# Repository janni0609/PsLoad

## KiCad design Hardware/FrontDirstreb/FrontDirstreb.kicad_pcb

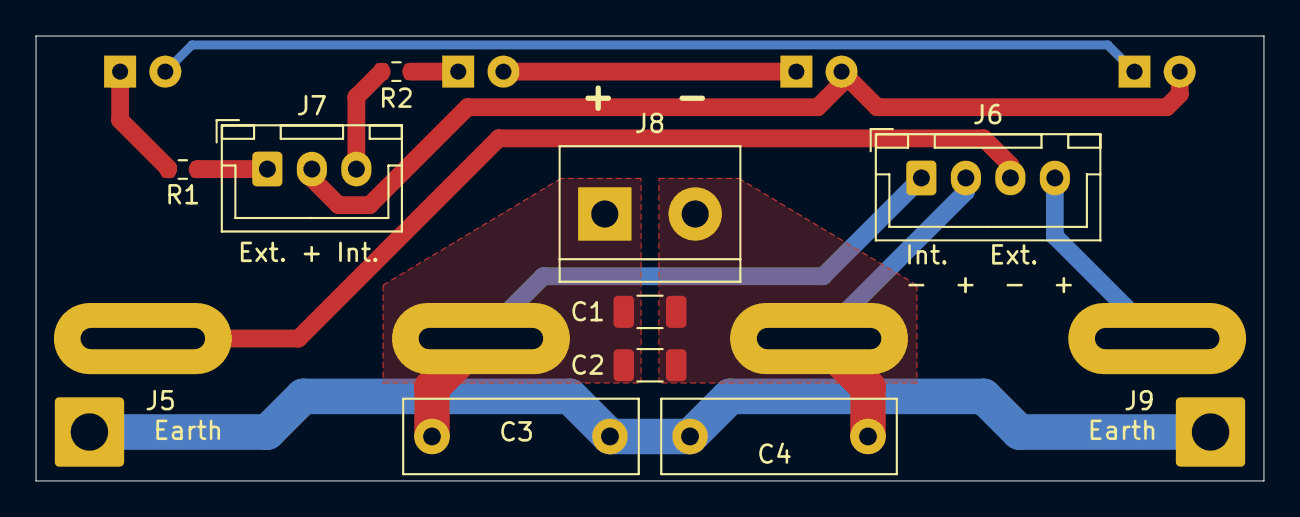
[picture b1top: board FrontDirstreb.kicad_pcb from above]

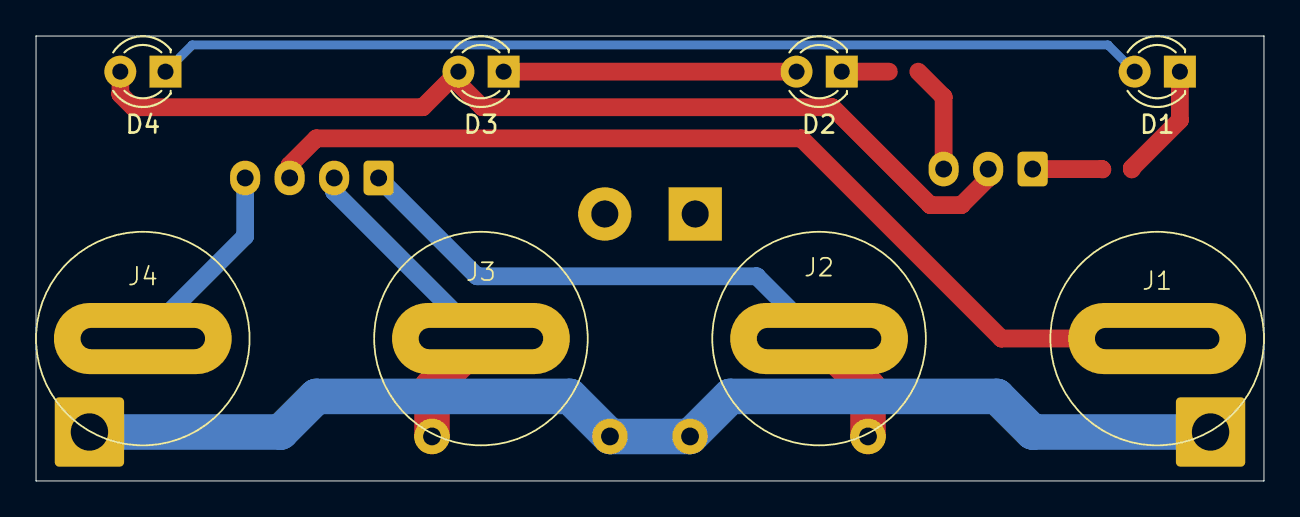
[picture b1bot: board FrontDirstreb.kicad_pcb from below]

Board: 2 copper layers, 69.0 x 25.0 mm, 19 parts (8 on the bottom side), 12 nets.

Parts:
C1, C2: 100n; C_1206_3216Metric
C3, C4: Y; C_Rect_L13.0mm_W4.0mm_P10.00mm_FKS3_FKP3_MKS4
D1, D2, D3, D4: LED; LED_D3.0mm_FlatTop
J1, J2, J3, J4: Banana; BananaSocket
J5, J9: Earth; SolderWire-1.5sqmm_1x01_D1.7mm_OD3.9mm
J6: Sense; JST_XH_B4B-XH-A_1x04_P2.50mm_Vertical
J7: LED; JST_XH_B3B-XH-A_1x03_P2.50mm_Vertical
J8: Power; TerminalBlock_bornier-2_P5.08mm
R1, R2: 49; R_0603_1608Metric

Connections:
/Ch1Pw+: C1.2, C2.2, C4.1, J3.1, J6.2, J8.2
/Ch1Pw-: C1.1, C2.1, C3.1, J2.1, J6.1, J8.1
Earth: C3.2, C4.2, J5.1, J9.1
unnamed: D1.2 (A), D4.1 (K)
unnamed: D1.1 (K), R1.2
unnamed: D2.2 (A), D3.1 (K)
unnamed: D2.1 (K), R2.2
unnamed: D3.2 (A), D4.2 (A), J7.2
unnamed: J1.1, J6.3
unnamed: J4.1, J6.4
unnamed: J7.1, R1.1
unnamed: J7.3, R2.1
